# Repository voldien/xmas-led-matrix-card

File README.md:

# Christmas LED Board

Remark that the schematic and PCB layout and the software driver are still work in progress and still have bugs both in the hardware and software.

# Motivation

## Installation

### Unix
The driver for *UNIX* system can be installed as followed:
```
make 
make install
```

# License
The source code for this project is licensed under the GPL+3 License - see the [LICENSE](LICENSE) file for details.
The hardware design for this project is under the OSHW License - See  for more detials.

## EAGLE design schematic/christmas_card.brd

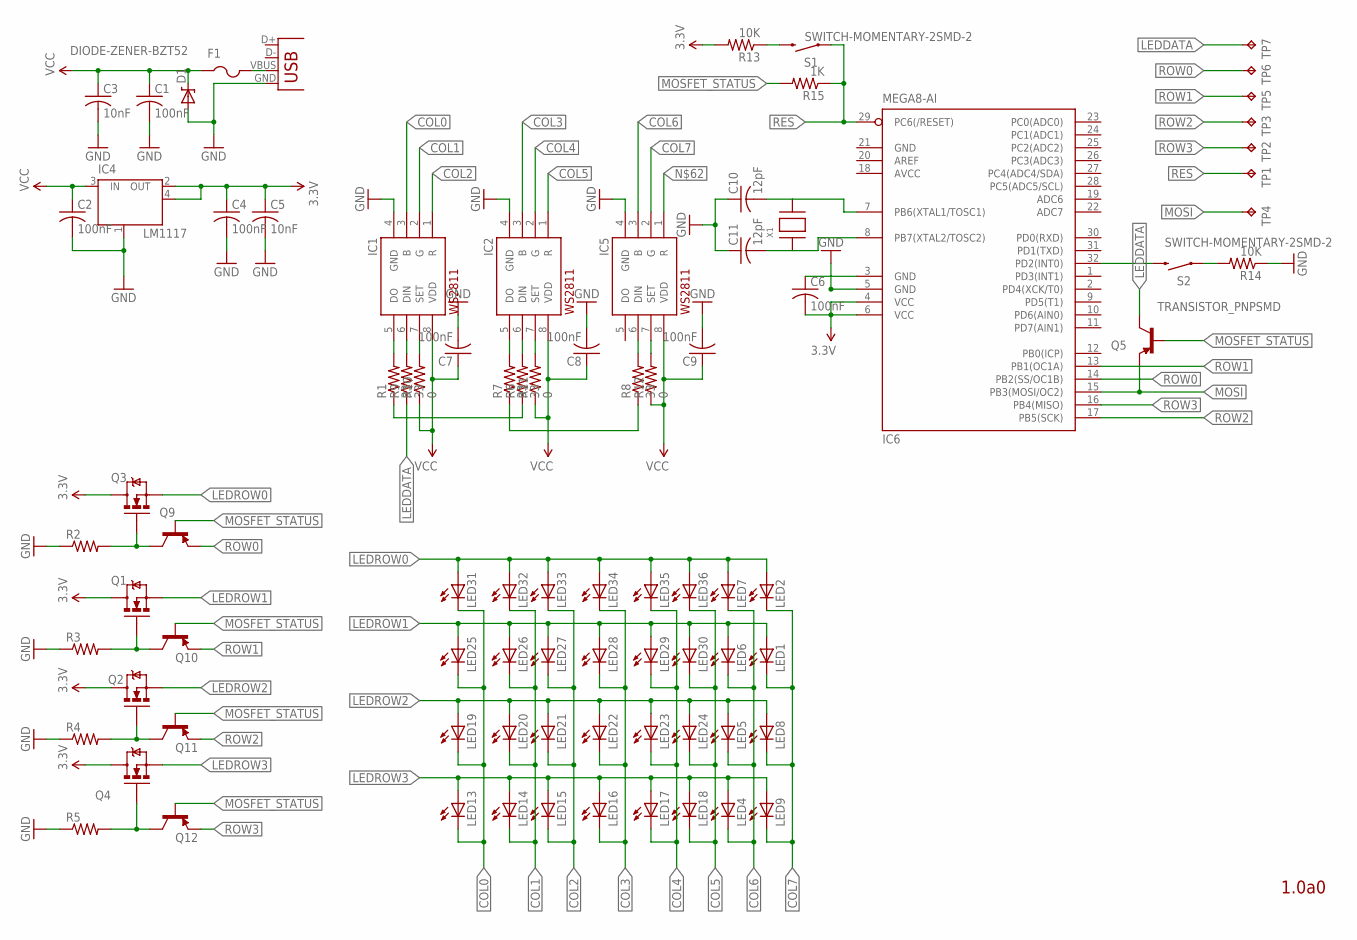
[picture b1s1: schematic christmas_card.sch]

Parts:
C1, C2, C4, C6, C7, C8, C9: 100nF; C0603
C3, C5: 10nF; C0603
C10, C11: 12pF; C0603
D1: DIODE-ZENER-BZT52; SOD-323
F1: PTCFUSE-1206; R1206
IC1, IC2, IC5: WS2811-SOP8; SO08-SKINNYPADS
IC4: LM1117; SOT223
IC6: MEGA8-AI; TQFP32-08
LED1, LED2, LED4, LED5, LED6, LED7, LED8, LED9, LED13, LED14, LED15, LED16, LED17, LED18, LED19, LED20, LED21, LED22, LED23, LED24, LED25, LED26, LED27, LED28, LED29, LED30, LED31, LED32, LED33, LED34, LED35, LED36: LED1206; LED-1206
Q1, Q2, Q3, Q4: MOSFET-NCHANNELSMD; SOT23-3
Q5, Q9, Q10, Q11, Q12: TRANSISTOR_PNPSMD; SOT23-3
R1, R6, R7, R8, R9: 33; R0603
R2, R3, R4, R5: R-US_R0603; R0603
R10, R11, R12: 0; R0603
R13, R14: 10K; R0603
R15: 1K; R0603
S1, S2: SWITCH-MOMENTARY-2SMD-2; TACTILE_SWITCH_SMD-2
TP1, TP2, TP3, TP4, TP5, TP6, TP7: TPB1,27; B1,27
X1: XTALNX5032; NX5032
X2: USB-MICROB

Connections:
3.3V: C4.1, C5.1, C6.2, IC4.2 (OUT), IC4.4 (OUT), IC6.4 (VCC), IC6.6 (VCC), Q1.3 (D), Q2.3 (D), Q3.3 (D), Q4.3 (D), R13.2
AVCC: IC6.18 (AVCC)
COL0: IC1.3 (B), LED13.C, LED19.C, LED25.C, LED31.C
COL1: IC1.2 (G), LED14.C, LED20.C, LED26.C, LED32.C
COL2: IC1.1 (R), LED15.C, LED21.C, LED27.C, LED33.C
COL3: IC2.3 (B), LED16.C, LED22.C, LED28.C, LED34.C
COL4: IC2.2 (G), LED17.C, LED23.C, LED29.C, LED35.C
COL5: IC2.1 (R), LED18.C, LED24.C, LED30.C, LED36.C
COL6: IC5.3 (B), LED4.C, LED5.C, LED6.C, LED7.C
COL7: IC5.2 (G), LED1.C, LED2.C, LED8.C, LED9.C
GND: C1.2, C2.2, C3.2, C4.2, C5.2, C6.1, C7.2, C8.2, C9.2, C10.1, C11.1, D1.2 (A), IC1.4 (GND), IC2.4 (GND), IC4.1 (GND/ADJ), IC5.4 (GND), IC6.3 (GND), IC6.5 (GND), IC6.21 (GND), R2.1, R3.1, R4.1, R5.1, R14.1, X2.GND
LEDDATA: Q5.3 (C), R9.1, TP7.TP
LEDROW0: LED2.A, LED7.A, LED31.A, LED32.A, LED33.A, LED34.A, LED35.A, LED36.A, Q3.2 (S)
LEDROW1: LED1.A, LED6.A, LED25.A, LED26.A, LED27.A, LED28.A, LED29.A, LED30.A, Q1.2 (S)
LEDROW2: LED5.A, LED8.A, LED19.A, LED20.A, LED21.A, LED22.A, LED23.A, LED24.A, Q2.2 (S)
LEDROW3: LED4.A, LED9.A, LED13.A, LED14.A, LED15.A, LED16.A, LED17.A, LED18.A, Q4.2 (S)
MOSFET_STATUS: Q5.1 (B), Q9.1 (B), Q10.1 (B), Q11.1 (B), Q12.1 (B), R15.2
MOSI: IC6.15 (PB3(MOSI/OC2)), Q5.2 (E), TP4.TP
unnamed: R1.1, R6.1
unnamed: IC1.5 (DO), R1.2
unnamed: IC2.6 (DIN), R6.2
unnamed: IC2.5 (DO), R7.2
unnamed: R7.1, R8.1
unnamed: IC5.6 (DIN), R8.2
unnamed: IC1.6 (DIN), R9.2
unnamed: IC5.7 (SET), R12.2
unnamed: R13.1, S1.1 (2)
unnamed: C10.2, IC6.7 (PB6(XTAL1/TOSC1)), X1.P$2
unnamed: IC6.32 (PD2(INT0)), S2.1 (2)
unnamed: R14.2, S2.2 (1)
unnamed: Q3.1 (G), Q9.3 (C), R2.2
unnamed: C11.2, IC6.8 (PB7(XTAL2/TOSC2)), X1.P$1
unnamed: IC2.7 (SET), R11.2
unnamed: IC1.7 (SET), R10.2
unnamed: F1.2, X2.VBUS
RES: IC6.29 (PC6(/RESET)), R15.1, S1.2 (1), TP1.TP
ROW0: IC6.14 (PB2(SS/OC1B)), Q9.2 (E), TP6.TP
ROW1: IC6.13 (PB1(OC1A)), Q1.1 (G), Q10.2 (E), Q10.3 (C), R3.2, TP5.TP
ROW2: IC6.17 (PB5(SCK)), Q2.1 (G), Q11.2 (E), Q11.3 (C), R4.2, TP3.TP
ROW3: IC6.16 (PB4(MISO)), Q4.1 (G), Q12.2 (E), Q12.3 (C), R5.2, TP2.TP
VCC: C1.1, C2.1, C3.1, C7.1, C8.1, C9.1, D1.1 (C), F1.1, IC1.8 (VDD), IC2.8 (VDD), IC4.3 (IN), IC5.8 (VDD), R10.1, R11.1, R12.1

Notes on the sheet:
1.0a0

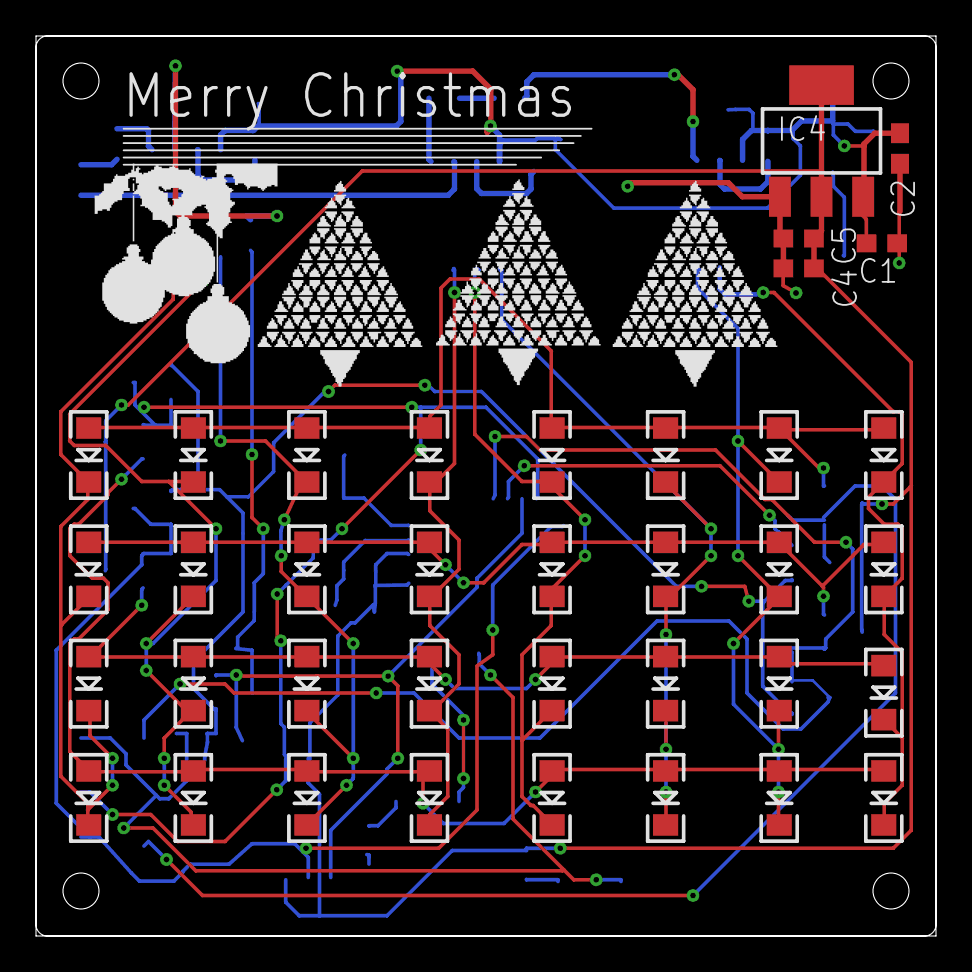
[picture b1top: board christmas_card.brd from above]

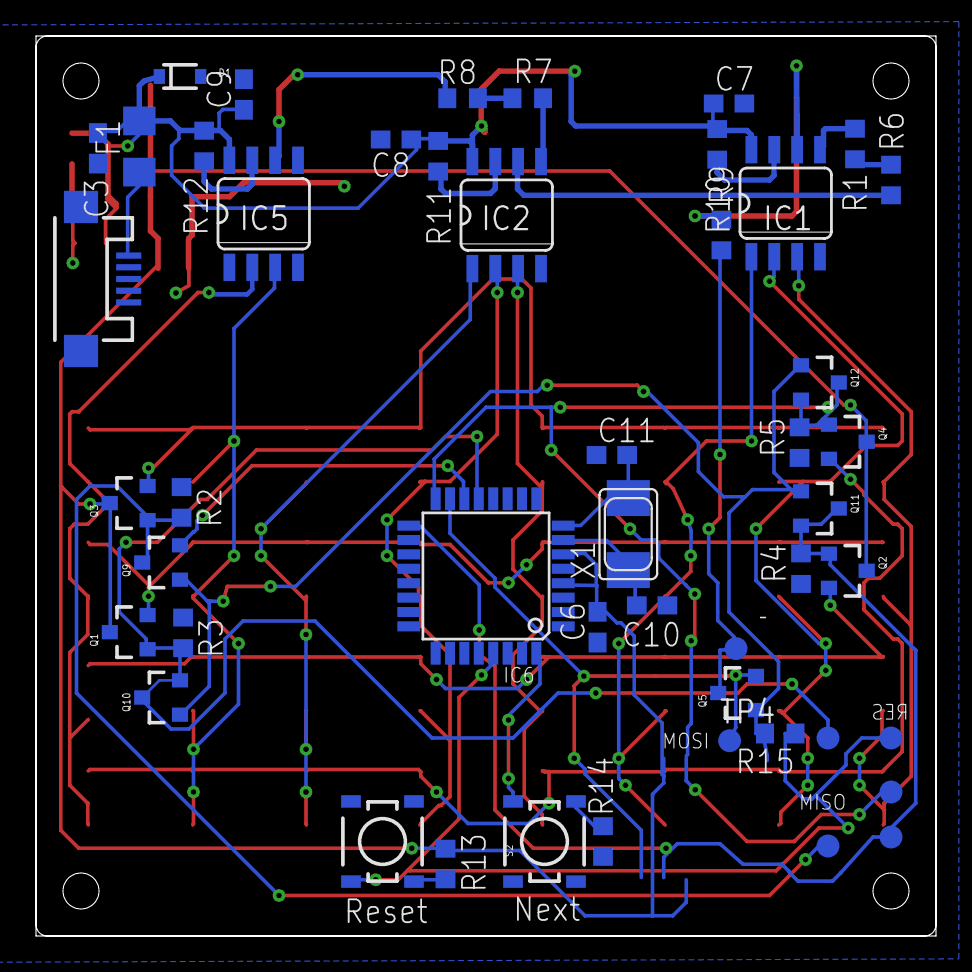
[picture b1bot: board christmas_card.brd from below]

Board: 2 copper layers, 50.0 x 50.0 mm, 85 parts (48 on the bottom side), 40 nets.

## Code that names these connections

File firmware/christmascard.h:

/**
	Simple Christmascard MCU driver.
	Copyright (C) 2017  Valdemar Lindberg

	This program is free software: you can redistribute it and/or modify
	it under the terms of the GNU General Public License as published by
	the Free Software Foundation, either version 3 of the License, or
	(at your option) any later version.

	This program is distributed in the hope that it will be useful,
	but WITHOUT ANY WARRANTY; without even the implied warranty of
	MERCHANTABILITY or FITNESS FOR A PARTICULAR PURPOSE.  See the
	GNU General Public License for more details.

	You should have received a copy of the GNU General Public License
	along with this program.  If not, see <http://www.gnu.org/licenses/>.

*/
#ifndef _CHRISTMAS_CARD_H_
#define _CHRISTMAS_CARD_H_ 1
#include<stdio.h>

/**
 *	constant global attributes.
 */
#define ROW0 (1 << PB2)
#define ROW1 (1 << PB1)
#define ROW2 (1 << PB5)
#define ROW3 (1 << PB4)
#define ROWALL (ROW0 | ROW1 | ROW2 | ROW3)
#define ROWPORT PORTB
#define ROWDPORT DDRB
#define NUMROWS 4
#define NUMCOL 8

/**
 *
 */
#define BUTTON_NEXT (1 << PD2)
#define WS2811_PIN	PB3
#define WS2811_IN (1 << WS2811_PIN)

/**
 *	Animation and LED.
 */
extern void cc_set_row(const uint8_t r);		/*	Set current enabled row.	*/
extern void cc_set_col(const uint8_t* d);		/*	Update LED driver with 8 bytes for current row.	*/
extern void cc_display_next_keyframe(void);		/*	Display next current key frame.	*/
extern void cc_select_led_controller(void);		/*	Select LED controller.	*/
extern void cc_select_flash_controller(void);	/*	Select Flash Controller.	*/

/**
 *	Button, controller and timers.
 */
extern void cc_init_nextanibutton(void);	/*	Initialize next animation button interrupt.	*/
extern void cc_init_ledcontrollers(void);	/*	Initialize LED controller.	*/
extern void cc_init_time2ovf(void);			/*	Enable timer overflow interrupt for update.	*/

#endif

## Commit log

2017-12-05 Added license file.
2020-10-02 Added init source files.
2020-10-02 Updated.
2021-03-13 Update README.md
    Added image of the work in progress board.

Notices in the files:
parts and their libraries:
SparkFun: Licensing: CC v3.0 Share-Alike You are welcome to use this library for commercial purposes.
